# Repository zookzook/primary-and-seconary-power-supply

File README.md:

# primary-and-seconary-power-supply
Schema for a primary and secondary power supply (dc, 12-24V)

## Basic idea

Based on two voltage sources, this circuit ensures that one of them is prioritized. The primary power source is a transformer operated by a generator. As soon as the generator is switched off, the second voltage source should be activated. In this case, the second power source is a battery powered by a solar module.

Two LEDs indicate the voltage source. One LED for the transformer (generator) and one for the battery. The voltage sources are designed for 12 or 24 volts.

A P-Channel Mosfet, as an ideal diode, ensures that the battery is only let through when the transformer is switched off. When the transformer is switched on, the mosfet closes and the battery is no longer used. In this case, the battery can be charged by the solar module without consumption.

The circuit can also be realized by a relay, but a higher power consumption by the relay itself must be considered. In addition, a relay usually costs a little more money.

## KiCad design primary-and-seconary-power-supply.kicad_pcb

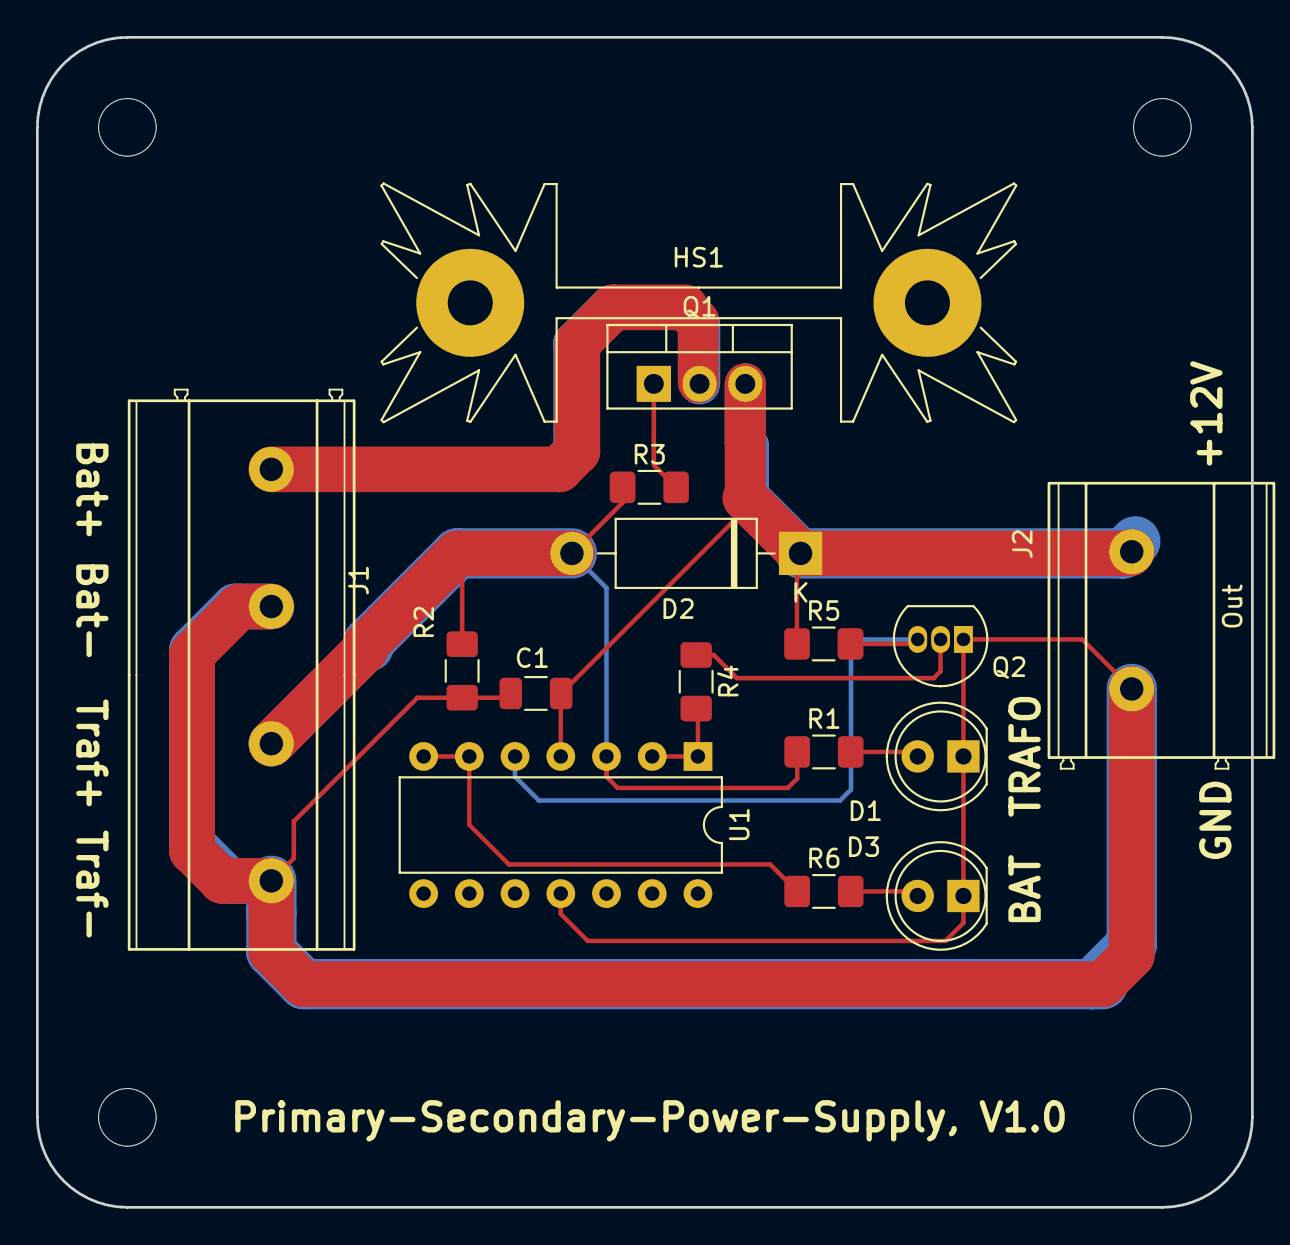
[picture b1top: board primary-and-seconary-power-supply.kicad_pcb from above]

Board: 2 copper layers, 67.5 x 65.0 mm, 16 parts (0 on the bottom side), 11 nets.

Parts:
C1: C; C_1206_3216Metric
D1, D3: LED; LED_D5.0mm
D2: D; D_DO-15_P12.70mm_Horizontal
HS1: Heatsink; Heatsink_Fischer_SK104-STC-STIC_35x13mm_2xDrill2.5mm
J1: In; Phoenix_Contact_MKDS_5-4-7,62
J2: Out; Phoenix_Contact_MKDS_5-2-7,62
Q1: Q_PMOS_GDS; TO-220-3_Vertical
Q2: Q_NPN_EBC; TO-92_Inline
R1: R; R_1206_3216Metric_Pad1.42x1.75mm_HandSolder
R2, R5: 100k; R_1206_3216Metric_Pad1.42x1.75mm_HandSolder
R3: 100; R_1206_3216Metric_Pad1.42x1.75mm_HandSolder
R4: 47k; R_1206_3216Metric_Pad1.42x1.75mm_HandSolder
R6: 220; R_1206_3216Metric_Pad1.42x1.75mm_HandSolder
U1: LM324; DIP-14_W7.62mm

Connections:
/BAT+: J1.1, Q1.2
/TRAFO+: D2.2, J1.3, R1.1, R2.1, R3.2, U1.3
GND: C1.2, D1.1, D3.1, J1.2, J1.4, J2.1, Q2.1, R2.2, U1.11
unnamed: D1.2, R1.2
unnamed: D3.2, R6.2
unnamed: Q1.1, R3.1
unnamed: Q2.2, R4.1
unnamed: Q2.3, R5.2, U1.5
unnamed: R4.2, U1.1, U1.2
unnamed: R6.1, U1.6, U1.7
VDD: C1.1, D2.1, J2.2, Q1.3, R5.1, U1.4

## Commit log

2019-06-09 Initial version
2019-06-10 updated documentation
